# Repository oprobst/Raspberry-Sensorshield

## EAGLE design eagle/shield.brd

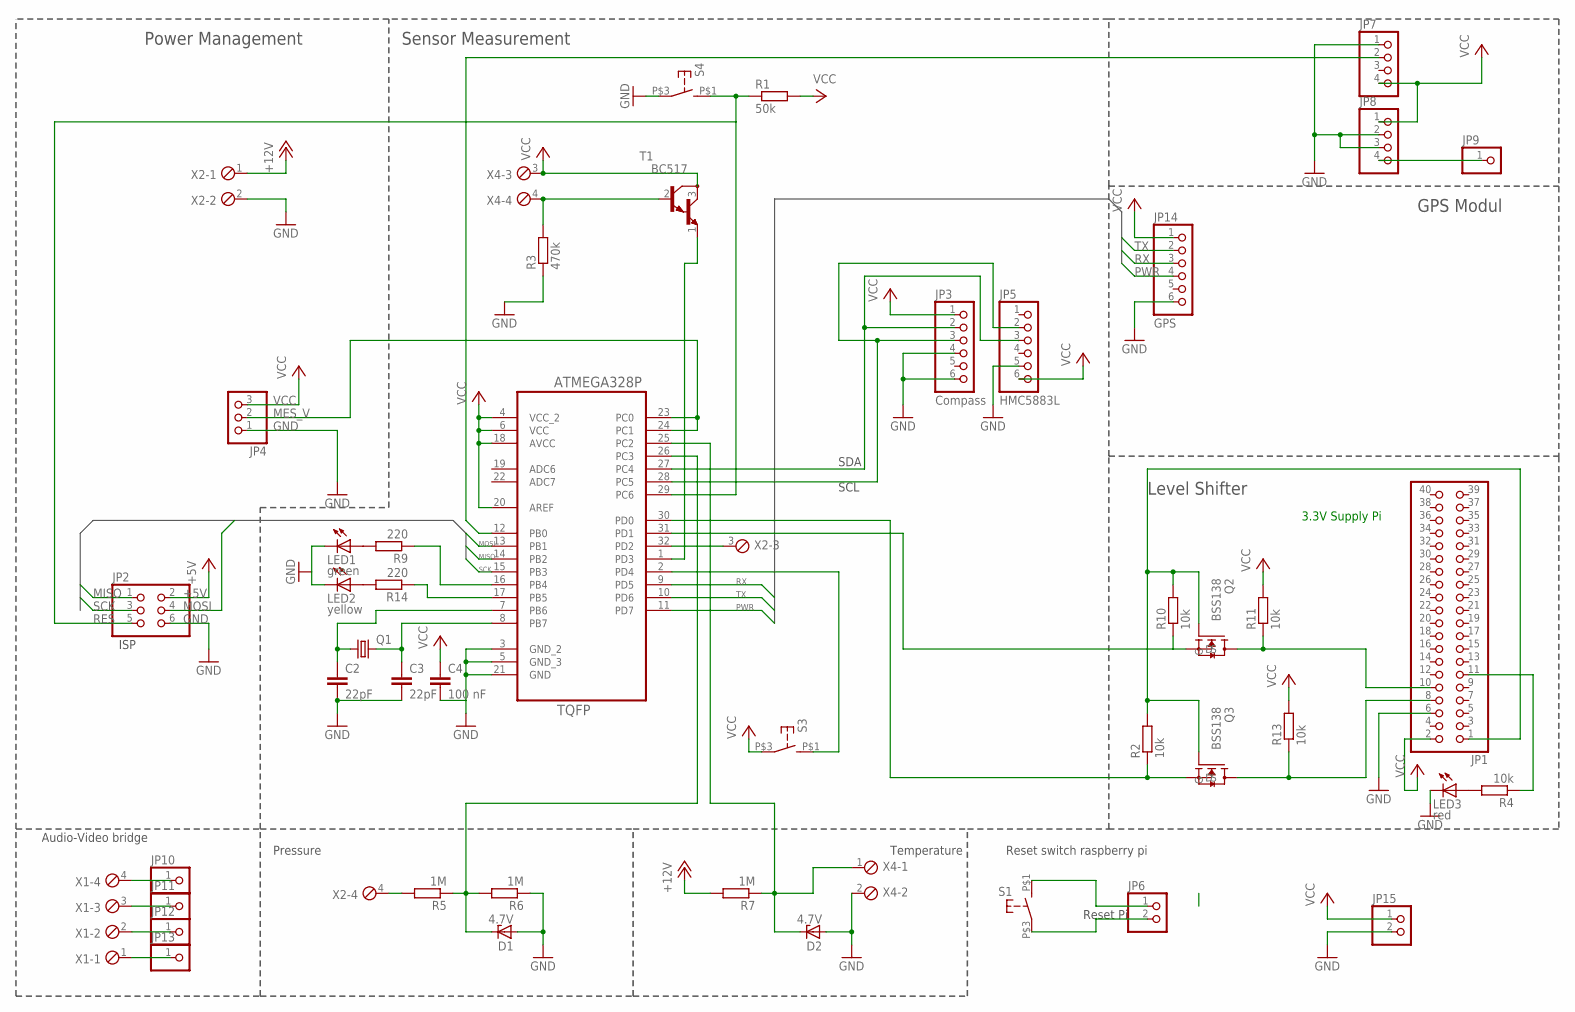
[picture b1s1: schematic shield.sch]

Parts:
C2, C3: 22pF; C1206
C4: 100 nF; C0603
D1, D2: 4.7V; SOT23
IC1: ATMEGA328P-AU; QFP80P900X900X120-32N
JP1: PINHD-2X20; 2X20
JP2: PINHD-2X3; 2X03
JP3: Compass; 1X06
JP4: PINHD-1X3; 1X03
JP5: HMC5883L; 1X06
JP6, JP15: PINHD-1X2; 1X02
JP7, JP8: PINHD-1X4; 1X04
JP9, JP10, JP11, JP12, JP13: PINHD-1X1; 1X01
JP14: GPS; 1X06
LED1: green; LED3MM
LED2: yellow; LED3MM
LED3: red; LED3MM
Q1: CRYSTALHC49UP; HC49UP
Q2, Q3: BSS138
R1: 50k; R1206
R2, R4, R10, R11, R13: 10k; R1206
R3: 470k; R1206
R5, R6, R7: 1M; R1206
R9, R14: 220; R1206
S1, S3, S4: SCHLIESSER_TASTSCHALTER; NAMAE-JTP-1130
T1: BC517; TO92
X1, X2, X4: MPT4; 4POL254

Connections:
+5V: JP2.2
+12V: R7.2, X2.1
GND: C2.2, C3.2, C4.2, D1.1 (A), D2.1 (A), IC1.3 (GND_2), IC1.5 (GND_3), IC1.21 (GND), JP1.6, JP2.6, JP3.4, JP3.6, JP4.1, JP5.5, JP7.1, JP8.2, JP8.3, JP14.6, JP15.2, LED1.K (C), LED2.K (C), LED3.K (C), R3.1, R6.1, S4.P$3 (4), X2.2, X4.2
MES_V: IC1.23 (PC0), IC1.24 (PC1), JP4.2
MISO: IC1.14 (PB2), JP2.1
MOSI: IC1.13 (PB1), JP2.4
unnamed: R5.2, X2.4
unnamed: C3.1, IC1.8 (PB7), Q1.2
unnamed: C2.1, IC1.7 (PB6), Q1.1
unnamed: IC1.28 (PC5), JP3.3, JP5.2
unnamed: R3.2, T1.2 (B), X4.4
unnamed: IC1.17 (PB5), R14.1
unnamed: JP8.4, JP9.1
unnamed: IC1.32 (PD2), X2.3
unnamed: IC1.12 (PB0), JP7.2
unnamed: IC1.1 (PD3), T1.1 (E)
unnamed: LED3.A, R4.2
unnamed: JP10.1, X1.4
unnamed: JP11.1, X1.3
unnamed: JP12.1, X1.2
unnamed: JP13.1, X1.1
unnamed: JP1.11, R4.1
unnamed: IC1.2 (PD4), S3.P$1 (3)
unnamed: LED1.A, R9.2
unnamed: IC1.27 (PC4), JP3.2, JP5.3
unnamed: JP1.10, Q2.D, R11.1
unnamed: JP1.8, Q3.D, R13.1
unnamed: JP6.1, S1.P$1 (3)
unnamed: JP6.2, S1.P$3 (4)
unnamed: IC1.16 (PB4), R9.1
unnamed: LED2.A, R14.2
unnamed: IC1.31 (PD1), Q2.S, R10.1
unnamed: IC1.30 (PD0), Q3.S, R2.1
unnamed: JP1.1, Q2.G, Q3.G, R2.2, R10.2
PWR: IC1.11 (PD7), JP14.4
RES: IC1.29 (PC6), JP2.5, R1.1, S4.P$1 (3)
RESET: D1.3 (C), IC1.26 (PC3), R5.1, R6.2
RESET1: D2.3 (C), IC1.25 (PC2), R7.1, X4.1
RX: IC1.9 (PD5), JP14.3
SCK: IC1.15 (PB3), JP2.3
TX: IC1.10 (PD6), JP14.2
VCC: C4.1, IC1.4 (VCC_2), IC1.6 (VCC), IC1.18 (AVCC), IC1.20 (AREF), JP1.2, JP3.1, JP4.3, JP5.6, JP7.4, JP8.1, JP14.1, JP15.1, R1.2, R11.2, R13.2, S3.P$3 (4), T1.3 (C), X4.3

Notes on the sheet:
ISP
SDA
SCL
3.3V Supply Pi
Power Management
Sensor Measurement
Level Shifter
Reset Pi
GPS Modul
Pressure
Temperature
Audio-Video bridge
Reset switch raspberry pi

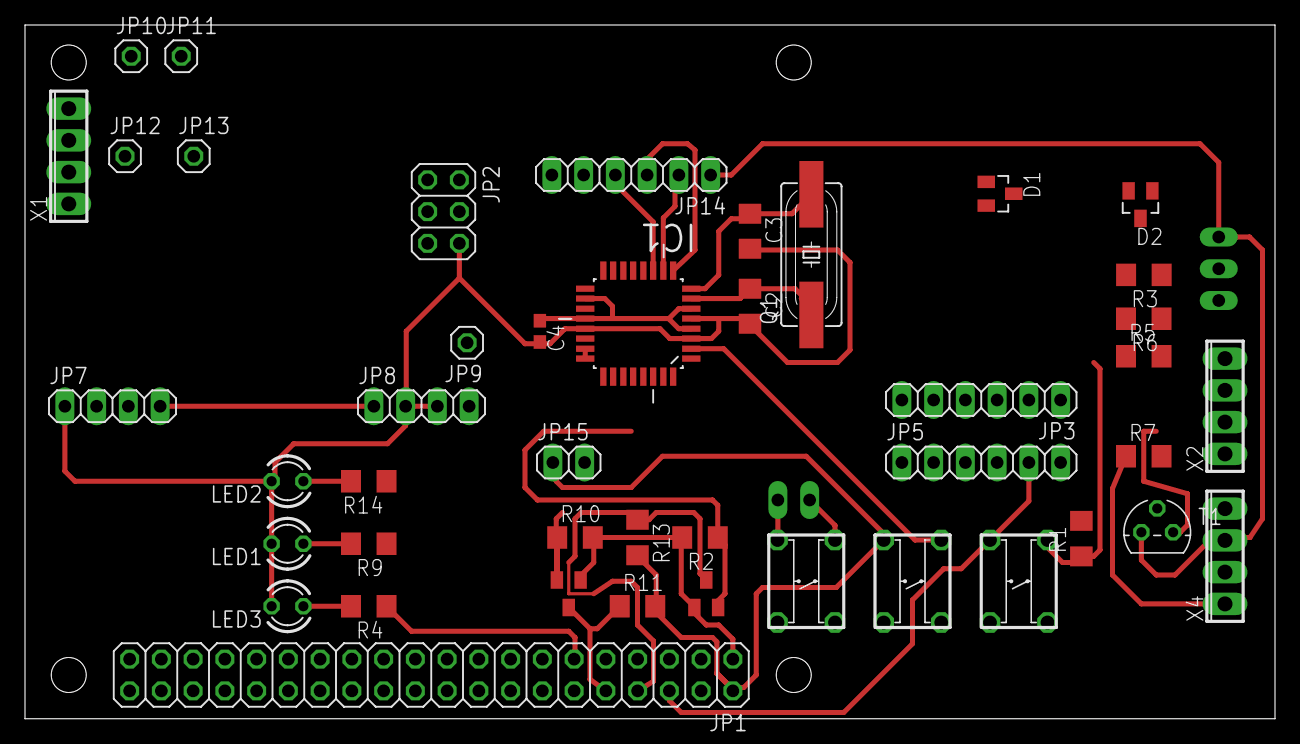
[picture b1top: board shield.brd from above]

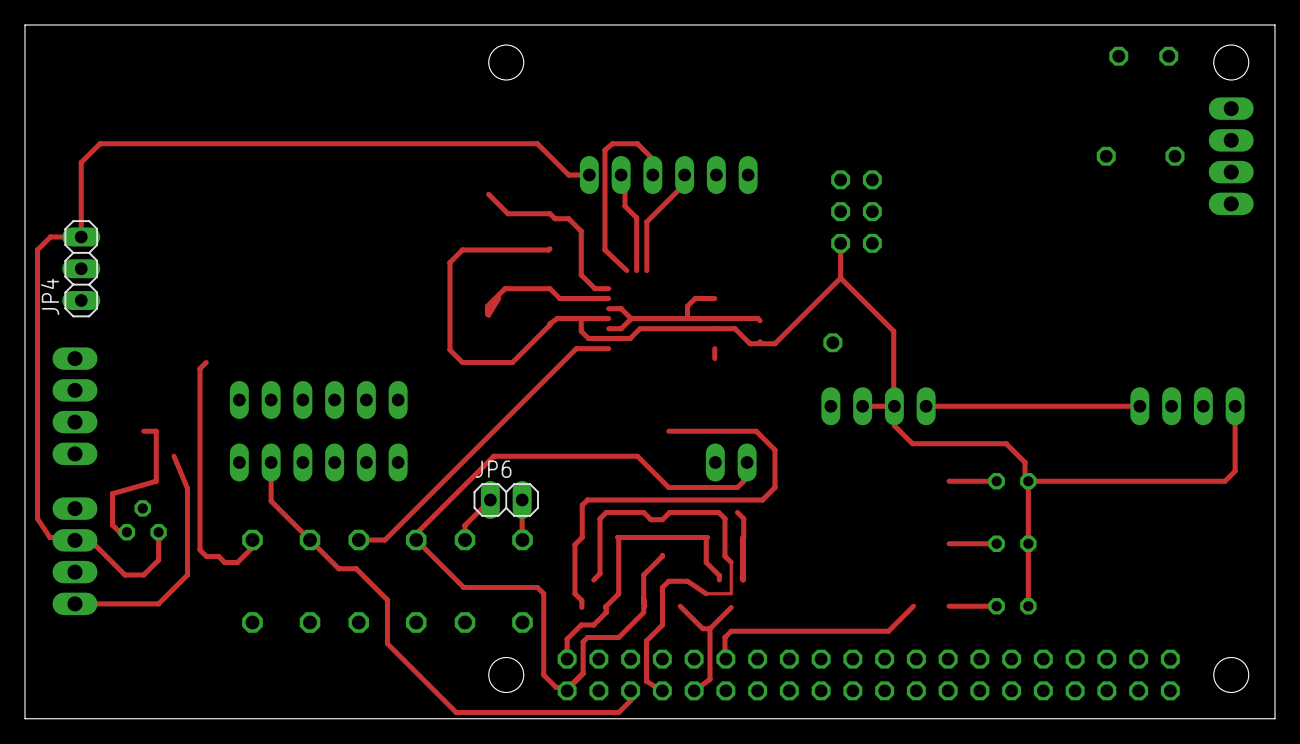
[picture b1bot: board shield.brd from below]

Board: 2 copper layers, 100.0 x 55.5 mm, 46 parts (2 on the bottom side), 41 nets.

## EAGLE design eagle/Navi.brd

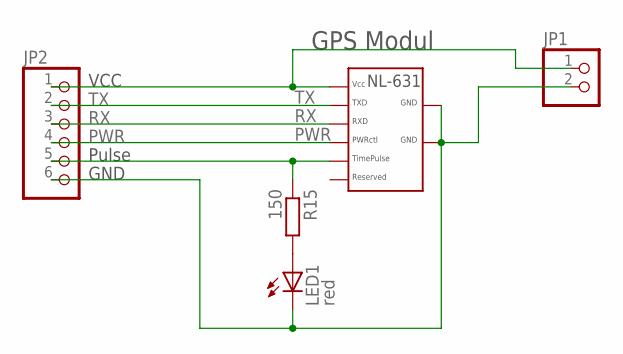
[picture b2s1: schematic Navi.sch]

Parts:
JP1: PINHD-1X2; 1X02
JP2: PINHD-1X6; 1X06
LED1: red; LED3MM
R15: 150; R1206
U$2: NAVILOK-NL-631ETTL

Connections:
GND: JP1.2, JP2.6, LED1.K (C), U$2.P$7, U$2.P$8
unnamed: JP1.1, JP2.1, U$2.P$1
unnamed: JP2.5, R15.1, U$2.P$5
unnamed: LED1.A, R15.2
PWR: JP2.4, U$2.P$4
RX: JP2.3, U$2.P$3
TX: JP2.2, U$2.P$2

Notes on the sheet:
GPS Modul
Pulse
GND
VCC

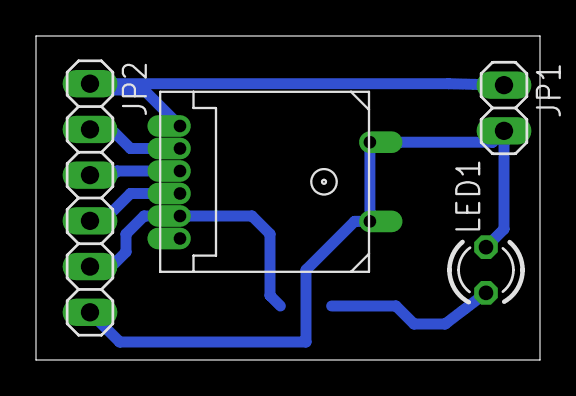
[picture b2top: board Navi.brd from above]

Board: 2 copper layers, 28.0 x 18.0 mm, 5 parts (1 on the bottom side), 7 nets.

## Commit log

2016-02-12 First schematic
2016-02-12 temporary copy
2016-02-12 added breakout for navi on an extra board
2016-02-12 first board design
